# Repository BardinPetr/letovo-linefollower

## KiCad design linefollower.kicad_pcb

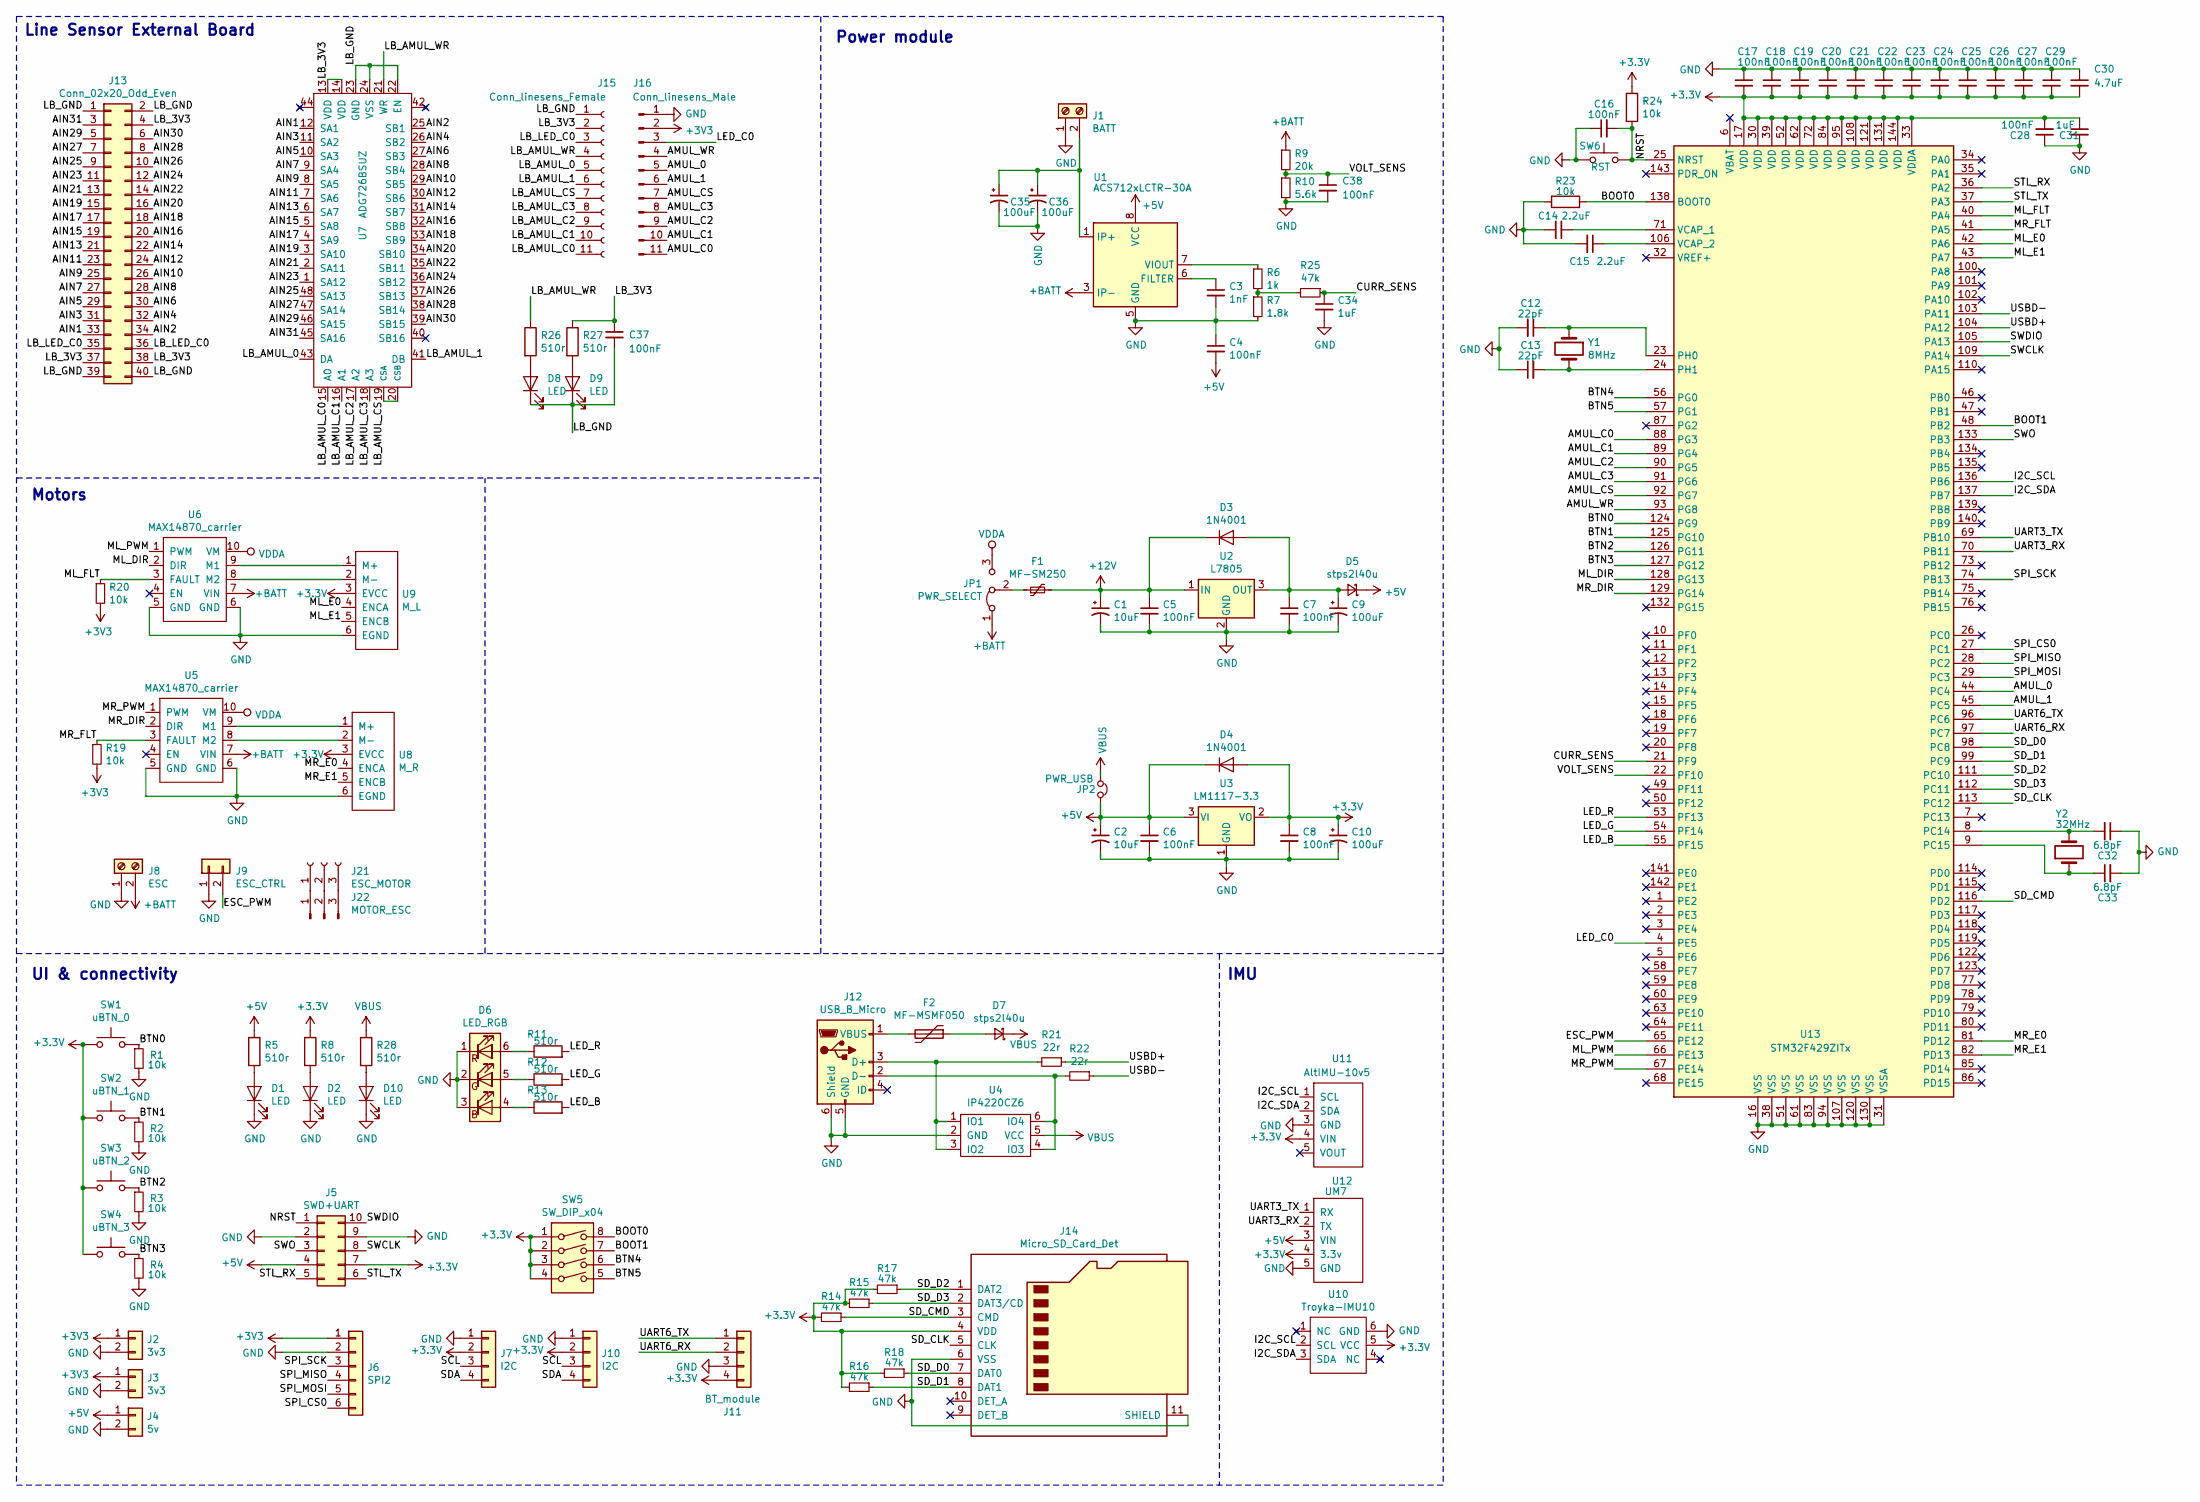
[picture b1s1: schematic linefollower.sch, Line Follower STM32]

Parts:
C1, C2: 10uF; CP_Elec_5x5.3
C3: 1nF; C_0805_2012Metric
C4, C5, C6, C7, C8, C16, C17, C18, C19, C20, C21, C22, C23, C24, C25, C26, C27, C28, C29, C37, C38: 100nF; C_0805_2012Metric
C9, C10, C35, C36: 100uF; CP_Elec_6.3x5.4
C12, C13: 22pF; C_0805_2012Metric
C14, C15: 2.2uF; C_0805_2012Metric
C30: 4.7uF; C_0805_2012Metric
C31, C34: 1uF; C_0805_2012Metric
C32, C33: 6.8pF; C_0805_2012Metric
D1, D2, D8, D9, D10: LED; LED_0603_1608Metric
D3, D4: 1N4001; D_DO-41_SOD81_P10.16mm_Horizontal
D5, D7: stps2l40u; D_SMB
D6: LED_RGB; LED_RGB_5050-6
F1: MF-SM250; MF-MSMF-A
F2: MF-MSMF050; MF-MSMF-A
J1: BATT; Soldered_pad_01x02_4x6
J2, J3: 3v3; PinSocket_1x02_P2.54mm_Vertical
J4: 5v; PinSocket_1x02_P2.54mm_Vertical
J5: SWD+UART; PinSocket_2x05_P2.54mm_Vertical
J6: SPI2; PinSocket_1x06_P2.54mm_Vertical
J7, J10: I2C; PinSocket_1x04_P2.54mm_Vertical
J8: ESC; Soldered_pad_01x02_4x6
J9: ESC_CTRL; PinSocket_1x02_P2.54mm_Vertical
J11: BT_module; PinSocket_1x04_P2.54mm_Vertical
J12: USB_B_Micro; USB_Micro-B_Amphenol_10103594-0001LF_Horizontal
J13: Conn_02x20_Odd_Even; PinSocket_2x20_P2.54mm_Vertical
J14: Micro_SD_Card_Det; microSD_HC_Hirose_DM3AT-SF-PEJM5
J15: Conn_linesens_Female; SolderedPad_1x11_P2.54
J16: Conn_linesens_Male; SolderedPad_1x11_P2.54
J21: ESC_MOTOR; Soldered_pad_01x03_4x5
J22: MOTOR_ESC; Soldered_pad_01x03_4x5
JP1: PWR_SELECT; SolderJumper-3_P1.3mm_Open_RoundedPad1.0x1.5mm
JP2: PWR_USB; SolderJumper-2_P1.3mm_Open_RoundedPad1.0x1.5mm
R1, R2, R3, R4, R19, R20, R23, R24: 10k; R_0805_2012Metric
R5, R8, R11, R12, R13, R26, R27, R28: 510r; R_0805_2012Metric
R6: 1k; R_0805_2012Metric
R7: 1.8k; R_0805_2012Metric
R9: 20k; R_0805_2012Metric
R10: 5.6k; R_0805_2012Metric
R14, R15, R16, R17, R18, R25: 47k; R_0805_2012Metric
R21, R22: 22r; R_0805_2012Metric
SW1: uBTN_0; SW_SPST_FSMSM
SW2: uBTN_1; SW_SPST_FSMSM
SW3: uBTN_2; SW_SPST_FSMSM
SW4: uBTN_3; SW_SPST_FSMSM
SW5: SW_DIP_x04; SW_DIP_SPSTx04_Slide_KingTek_DSHP04TS_W7.62mm_P1.27mm
SW6: RST; SW_SPST_FSMSM
U1: ACS712xLCTR-30A; SOIC-8_3.9x4.9mm_P1.27mm
U2: L7805; TO-263-3_TabPin2
U3: LM1117-3.3; TO-252-3_TabPin2
U4: IP4220CZ6; TSOP-6_1.65x3.05mm_P0.95mm
U5, U6: MAX14870_carrier; MAX14870_Carrier
U7: ADG726BSUZ; TQFP-48-1EP_7x7mm_P0.5mm_EP3.5x3.5mm
U8: M_R; JST_SH_BM06B-SRSS-TB_1x06-1MP_P1.00mm_Vertical
U9: M_L; JST_SH_BM06B-SRSS-TB_1x06-1MP_P1.00mm_Vertical
U10: Troyka-IMU10; Troyka_IMU
U11: AltIMU-10v5; AltIMU10_v5
U12: UM7; JST_SH_BM05B-SRSS-TB_1x05-1MP_P1.00mm_Vertical
U13: STM32F429ZITx; LQFP-144_20x20mm_P0.5mm
Y1: 8MHz; Crystal_SMD_3215-2Pin_3.2x1.5mm
Y2: 32MHz; Crystal_HC49-4H_Vertical

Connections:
+5V: C2.1, C4.2, C6.1, D4.1 (K), D5.1 (K), J4.1, J5.4, JP2.2, R5.1, U1.8 (VCC), U3.3 (VI), U12.3 (VIN)
+12V: C1.1, C5.1, D3.1 (K), F1.2, U2.1 (IN)
+BATT: J8.2, JP1.1 (A), R9.1, U1.3 (IP-), U1.4 (IP-), U5.7 (VIN), U6.7 (VIN)
/AIN1: J13.33, U7.12 (SA1)
/AIN2: J13.34, U7.25 (SB1)
/AIN3: J13.31, U7.11 (SA2)
/AIN4: J13.32, U7.26 (SB2)
/AIN5: J13.29, U7.10 (SA3)
/AIN6: J13.30, U7.27 (SB3)
/AIN7: J13.27, U7.9 (SA4)
/AIN8: J13.28, U7.28 (SB4)
/AIN9: J13.25, U7.8 (SA5)
/AIN10: J13.26, U7.29 (SB5)
/AIN11: J13.23, U7.7 (SA6)
/AIN12: J13.24, U7.30 (SB6)
/AIN13: J13.21, U7.6 (SA7)
/AIN14: J13.22, U7.31 (SB7)
/AIN15: J13.19, U7.5 (SA8)
/AIN16: J13.20, U7.32 (SB8)
/AIN17: J13.17, U7.4 (SA9)
/AIN18: J13.18, U7.33 (SB9)
/AIN19: J13.15, U7.3 (SA10)
/AIN20: J13.16, U7.34 (SB10)
/AIN21: J13.13, U7.2 (SA11)
/AIN22: J13.14, U7.35 (SB11)
/AIN23: J13.11, U7.1 (SA12)
/AIN24: J13.12, U7.36 (SB12)
/AIN25: J13.9, U7.48 (SA13)
/AIN26: J13.10, U7.37 (SB13)
/AIN27: J13.7, U7.47 (SA14)
/AIN28: J13.8, U7.38 (SB14)
/AIN29: J13.5, U7.46 (SA15)
/AIN30: J13.6, U7.39 (SB15)
/AIN31: J13.3, U7.45 (SA16)
/AMUL_0: J16.5, U13.44 (PC4)
/AMUL_1: J16.6, U13.45 (PC5)
/AMUL_C0: J16.11, U13.88 (PG3)
/AMUL_C1: J16.10, U13.89 (PG4)
/AMUL_C2: J16.9, U13.90 (PG5)
/AMUL_C3: J16.8, U13.91 (PG6)
/AMUL_CS: J16.7, U13.92 (PG7)
/AMUL_WR: J16.4, U13.93 (PG8)
/BOOT0: R23.1, SW5.8, U13.138 (BOOT0)
/BOOT1: SW5.7, U13.48 (PB2)
/BTN0: R1.1, SW1.2, U13.124 (PG9)
/BTN1: R2.1, SW2.2, U13.125 (PG10)
/BTN2: R3.1, SW3.2, U13.126 (PG11)
/BTN3: R4.1, SW4.2, U13.127 (PG12)
/BTN4: SW5.6, U13.56 (PG0)
/BTN5: SW5.5, U13.57 (PG1)
/CURR_SENS: C34.1, R25.1, U13.21 (PF9)
/ESC_PWM: J9.2, U13.65 (PE12)
/I2C_SCL: U10.2 (SCL), U11.1 (SCL), U13.136 (PB6)
/I2C_SDA: U10.3 (SDA), U11.2 (SDA), U13.137 (PB7)
/LB_3V3: C37.1, J13.4, J13.37, J13.38, J15.2, R27.1, U7.13 (VDD), U7.14 (VDD)
/LB_AMUL_0: J15.5, U7.43 (DA)
/LB_AMUL_1: J15.6, U7.41 (DB)
/LB_AMUL_C0: J15.11, U7.15 (A0)
/LB_AMUL_C1: J15.10, U7.16 (A1)
/LB_AMUL_C2: J15.9, U7.17 (A2)
/LB_AMUL_C3: J15.8, U7.18 (A3)
/LB_AMUL_CS: J15.7, U7.19 (CSA), U7.20 (CSB)
/LB_AMUL_WR: J15.4, R26.1, U7.21 (WR)
/LB_GND: C37.2, D8.1 (K), D9.1 (K), J13.1, J13.2, J13.39, J13.40, J15.1, U7.22 (EN), U7.23 (GND), U7.24 (VSS)
/LB_LED_C0: J13.35, J13.36, J15.3
/LED_B: R13.2, U13.55 (PF15)
/LED_C0: J16.3, U13.4 (PE5)
/LED_G: R12.2, U13.54 (PF14)
/LED_R: R11.2, U13.53 (PF13)
/ML_DIR: U6.2 (DIR), U13.128 (PG13)
/ML_E0: U9.4 (ENCA), U13.42 (PA6)
/ML_E1: U9.5 (ENCB), U13.43 (PA7)
/ML_FLT: R20.1, U6.3 (FAULT), U13.40 (PA4)
/ML_PWM: U6.1 (PWM), U13.66 (PE13)
/MR_DIR: U5.2 (DIR), U13.129 (PG14)
/MR_E0: U8.4 (ENCA), U13.81 (PD12)
/MR_E1: U8.5 (ENCB), U13.82 (PD13)
/MR_FLT: R19.1, U5.3 (FAULT), U13.41 (PA5)
/MR_PWM: U5.1 (PWM), U13.67 (PE14)
/NRST: C16.2, J5.1, R24.2, SW6.2, U13.25 (NRST)
/SCL: J7.3, J10.3
/SDA: J7.4, J10.4
/SD_CLK: J14.5 (CLK), U13.113 (PC12)
/SD_CMD: J14.3 (CMD), R14.1, U13.116 (PD2)
/SD_D0: J14.7 (DAT0), R18.1, U13.98 (PC8)
/SD_D1: J14.8 (DAT1), R16.1, U13.99 (PC9)
/SD_D2: J14.1 (DAT2), R17.1, U13.111 (PC10)
/SD_D3: J14.2 (DAT3/CD), R15.1, U13.112 (PC11)
/SPI_CS0: J6.6, U13.27 (PC1)
/SPI_MISO: J6.4, U13.28 (PC2)
/SPI_MOSI: J6.5, U13.29 (PC3)
/SPI_SCK: J6.3, U13.74 (PB13)
/STL_RX: J5.5, U13.36 (PA2)
/STL_TX: J5.6, U13.37 (PA3)
/SWCLK: J5.8, U13.109 (PA14)
/SWDIO: J5.10, U13.105 (PA13)
/SWO: J5.3, U13.133 (PB3)
/UART3_RX: U12.2 (TX), U13.70 (PB11)
/UART3_TX: U12.1 (RX), U13.69 (PB10)
/UART6_RX: J11.2, U13.97 (PC7)
/UART6_TX: J11.1, U13.96 (PC6)
/USBD+: R21.1, U13.104 (PA12)
/USBD-: R22.1, U13.103 (PA11)
/VOLT_SENS: C38.1, R9.2, R10.1, U13.22 (PF10)
GND: C1.2, C2.2, C3.2, C4.1, C5.2, C6.2, C7.2, C8.2, C9.2, C10.2, C12.2, C13.1, C14.2, C15.2, C16.1, C17.1, C18.1, C19.1, C20.1, C21.1, C22.1, C23.1, C24.1, C25.1, C26.1, C27.1, C28.1, C29.1, C30.1, C31.2, C32.1, C33.2, C34.2, C35.2, C36.2, C38.2, D1.1 (K), D2.1 (K), D6.1 (RK), D6.2 (GK), D6.3 (BK), D10.1 (K), J1.1, J2.2, J3.2, J4.2, J5.2, J5.9, J6.2, J7.1, J8.1, J9.1, J10.1, J11.3, J12.5 (GND), J12.6 (Shield), J14.6 (VSS), J14.11 (SHIELD), J16.1, R1.2, R2.2, R3.2, R4.2, R7.2, R10.2, R23.2, SW6.1, U1.5 (GND), U2.2 (GND), U3.1 (GND), U4.2 (GND), U5.5 (GND), U5.6 (GND), U6.5 (GND), U6.6 (GND), U8.6 (EGND), U9.6 (EGND), U10.6 (GND), U11.3 (GND), U12.5 (GND), U13.16 (VSS), U13.31 (VSSA), U13.38 (VSS), U13.51 (VSS), U13.61 (VSS), U13.83 (VSS), U13.94 (VSS), U13.107 (VSS), U13.120 (VSS), U13.130 (VSS)
unnamed: C3.1, U1.6 (FILTER)
unnamed: C7.1, C9.1, D3.2 (A), D5.2 (A), U2.3 (OUT)
unnamed: C12.1, U13.23 (PH0), Y1.1
unnamed: C13.2, U13.24 (PH1), Y1.2
unnamed: C14.1, U13.71 (VCAP_1)
unnamed: C15.1, U13.106 (VCAP_2)
unnamed: C32.2, U13.8 (PC14), Y2.2
unnamed: C33.1, U13.9 (PC15), Y2.1
unnamed: C35.1, C36.1, J1.2, U1.1 (IP+), U1.2 (IP+)
unnamed: D1.2 (A), R5.2
unnamed: D2.2 (A), R8.2
unnamed: D6.4 (BA), R13.1
unnamed: D6.5 (GA), R12.1
unnamed: D6.6 (RA), R11.1
unnamed: D7.2 (A), F2.1
unnamed: D8.2 (A), R26.2
unnamed: D9.2 (A), R27.2
unnamed: D10.2 (A), R28.2
unnamed: F1.1, JP1.2 (C)
unnamed: F2.2, J12.1 (VBUS)
unnamed: J12.2 (D-), R22.2, U4.4 (IO3), U4.6 (IO4)
unnamed: J12.3 (D+), R21.2, U4.1 (IO1), U4.3 (IO2)
unnamed: J21.1, J22.1
unnamed: J21.2, J22.2
unnamed: J21.3, J22.3
unnamed: R6.1, U1.7 (VIOUT)
unnamed: R6.2, R7.1, R25.2
unnamed: U5.8 (M2), U8.2 (M-)
unnamed: U5.9 (M1), U8.1 (M+)
unnamed: U6.8 (M2), U9.2 (M-)
unnamed: U6.9 (M1), U9.1 (M+)
VBUS: D7.1 (K), JP2.1, R28.1, U4.5 (VCC)
VDDA: JP1.3 (B), U5.10 (VM), U6.10 (VM)

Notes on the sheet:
Line Sensor External Board
Power module
Motors
UI & connectivity
IMU

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
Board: 2 copper layers, 128 parts (4 on the bottom side), 139 nets, no tracks yet.

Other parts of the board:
MH0, MH1, MH2, MH3, MH9, MH10: MountingHole_2.2mm_M2
MH5, MH6, MH7, MH8: MountingHole_2.2mm_M2_ISO7380

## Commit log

2020-03-15 Base scheme finished
2020-03-17 PDF added
2020-03-19 Added voltage & current sensing; Minor fixes
2020-03-19 Fixed footprints
2020-03-21 Minor schematic fixes - now RC; Basic PCB
2020-03-22 PCB for linesensor board and powermodule finished
2020-03-23 MCU's main peripherals PCB
2020-03-23 All PCB components places
2020-03-23 Finished connection of PCBs
2020-03-24 PCB minor improvements
